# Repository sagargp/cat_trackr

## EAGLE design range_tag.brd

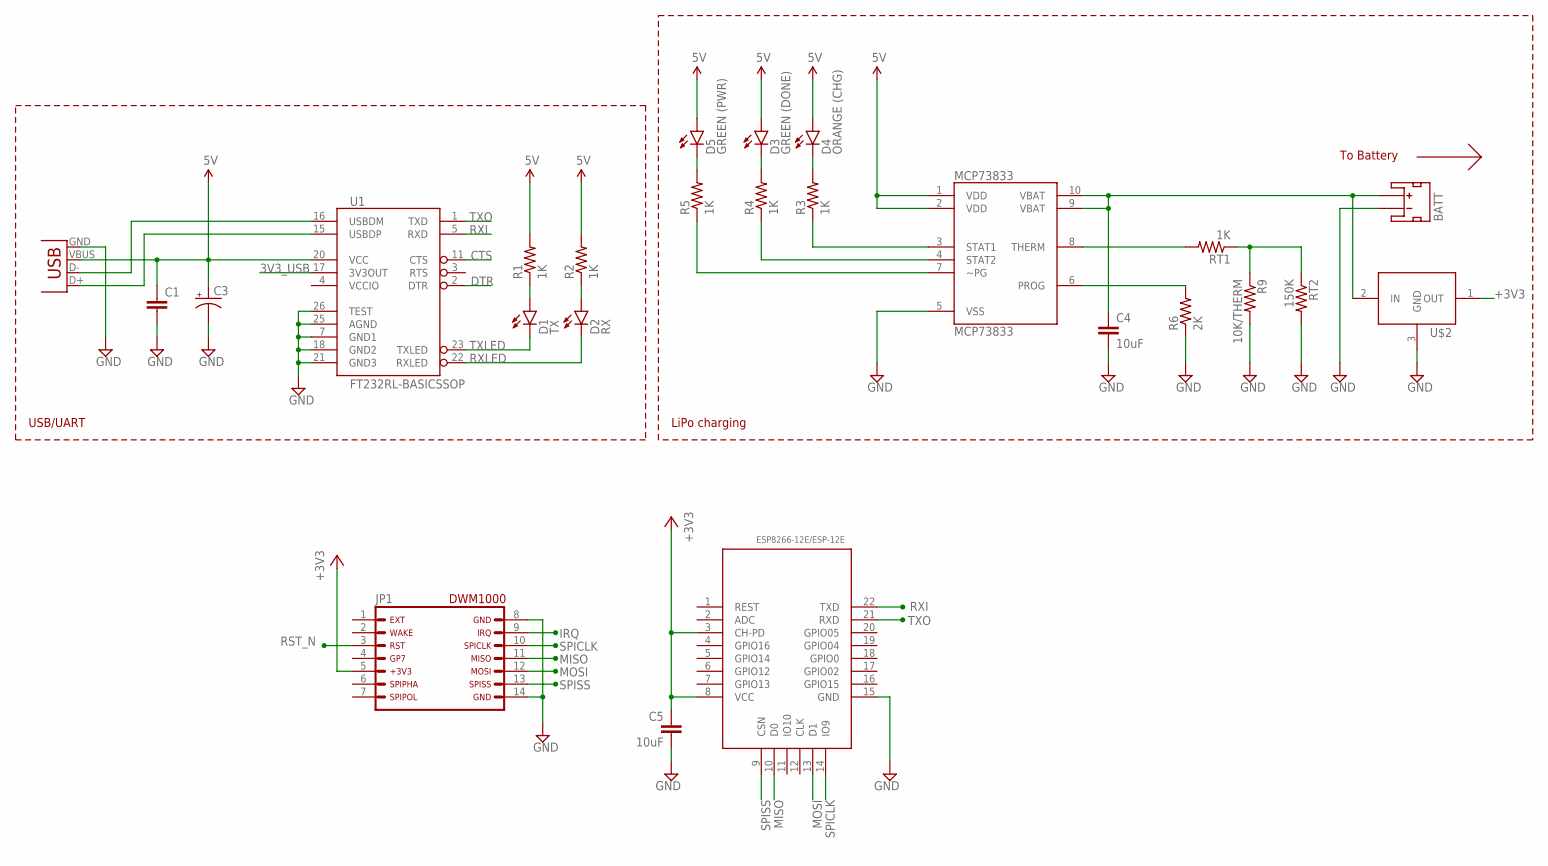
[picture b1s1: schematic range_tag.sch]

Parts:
BATT: JST_2MM_MALE; JST-2-SMD
C1: CAP0805; 0805
C3: CAP_POL1206-KIT; EIA3216-KIT
C4, C5: 10uF; 1206
D1: TX; LED-1206
D2: RX; LED-1206
D3: GREEN (DONE); LED-1206
D4: ORANGE (CHG); LED-1206
D5: GREEN (PWR); LED-1206
JP1: DWM1000-DIPDWM1000-BREAKOUT; 2X07_HOLES_ONLY
JP2: USB-SMD-NS; USB-MINIB-NOSTOP
MCP73833: MCP73833; MSOP-10
R1, R2, R3, R4, R5: 1K; 1206
R6: 2K; 1206
R9: 10K/THERM; 1206
RT1: 1K; 1206
RT2: 150K; 1206
U1: FT232RL-BASICSSOP; SSOP28DB
U3: ESP8266-12E/ESP-12E; LGA22-2.0-24X16MM
U$2: LM3480IM4; SOT23-3

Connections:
3V3_USB: U1.17 (3V3OUT)
5V: C1.1, C3.A (+), D3.A, D4.A, D5.A, JP2.VBUS, MCP73833.1 (VDD), MCP73833.2 (VDD), R1.2, R2.2, U1.20 (VCC)
+3V3: C5.1, JP1.5, U3.3 (CH-PD), U3.8 (VCC), U$2.1 (OUT)
CTS: U1.11 (CTS)
DTR: U1.2 (DTR)
GND: BATT.1 (-), C1.2, C3.C (-), C4.2, C5.2, JP1.8, JP1.14, JP2.GND, MCP73833.5 (VSS), R6.1, R9.2, RT2.2, U1.7 (GND1), U1.18 (GND2), U1.21 (GND3), U1.25 (AGND), U1.26 (TEST), U3.15 (GND), U$2.3 (GND)
IRQ: JP1.9
MISO: JP1.11, U3.10 (D0)
MOSI: JP1.12, U3.13 (D1)
unnamed: MCP73833.8 (THERM), RT1.2
unnamed: R9.1, RT1.1, RT2.1
unnamed: D3.C, R4.2
unnamed: D4.C, R3.2
unnamed: D1.A, R1.1
unnamed: D2.A, R2.1
unnamed: D5.C, R5.2
unnamed: MCP73833.6 (PROG), R6.2
N_PG: MCP73833.7 (~PG), R5.1
RST_N: JP1.3
RXI: U1.5 (RXD), U3.22 (TXD)
RXLED: D2.C, U1.22 (RXLED)
SPICLK: JP1.10, U3.14 (IO9)
SPISS: JP1.13, U3.9 (CSN)
STAT1: MCP73833.3 (STAT1), R3.1
STAT2: MCP73833.4 (STAT2), R4.1
TXLED: D1.C, U1.23 (TXLED)
TXO: U1.1 (TXD), U3.21 (RXD)
USBDM: JP2.D-, U1.16 (USBDM)
USBDP: JP2.D+, U1.15 (USBDP)
VCCIO: U1.4 (VCCIO)
V_BATT: BATT.2 (+), C4.1, MCP73833.9 (VBAT), MCP73833.10 (VBAT), U$2.2 (IN)

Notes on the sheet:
USB/UART
LiPo charging
To Battery

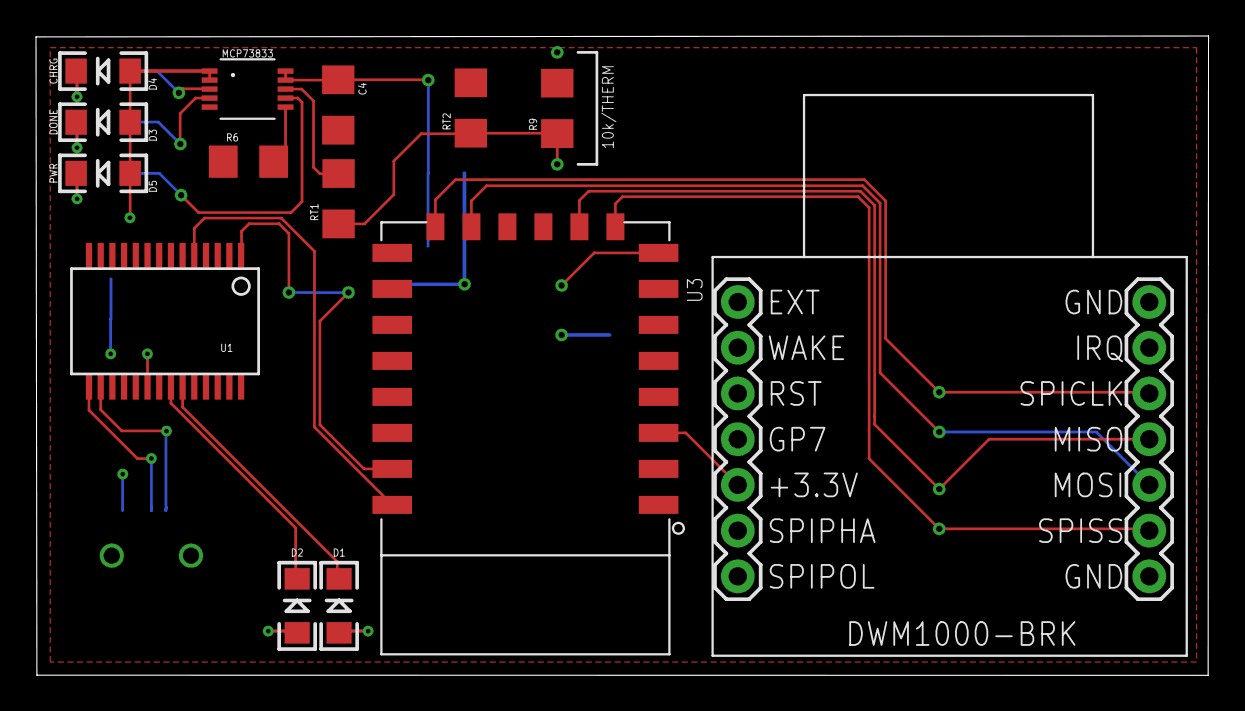
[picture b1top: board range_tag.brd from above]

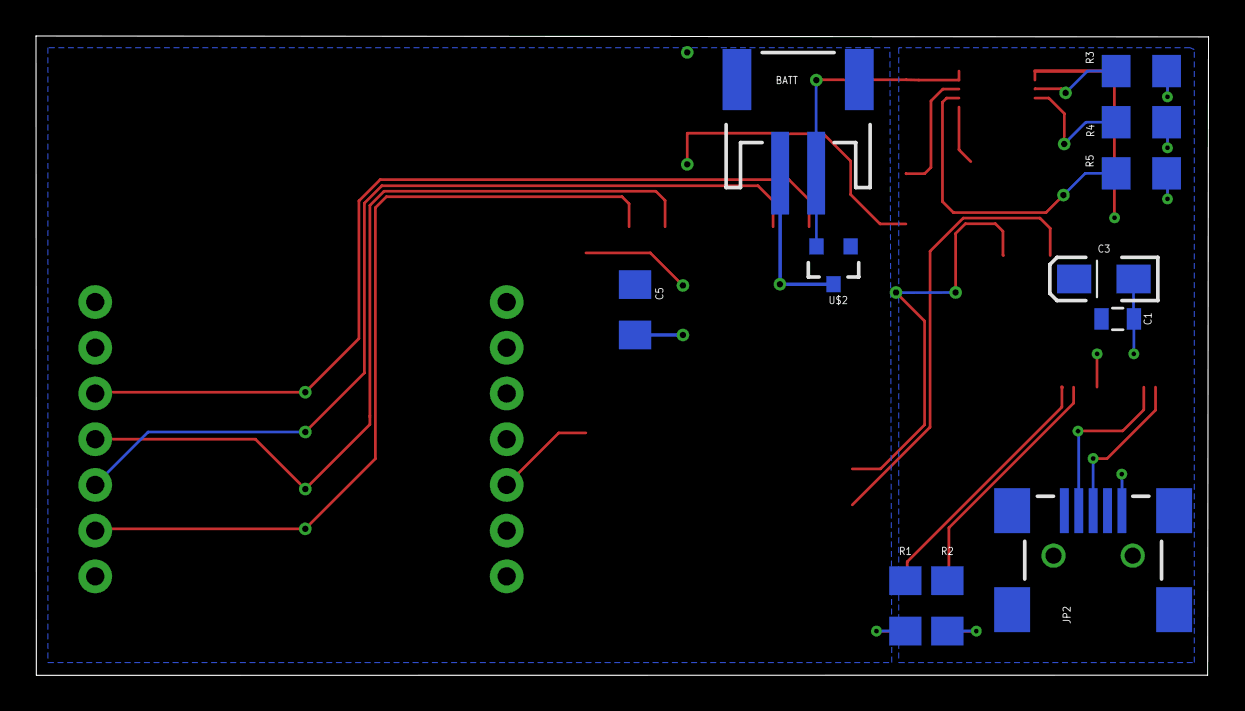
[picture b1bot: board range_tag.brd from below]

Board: 2 copper layers, 65.1 x 35.5 mm, 25 parts (11 on the bottom side), 25 nets.

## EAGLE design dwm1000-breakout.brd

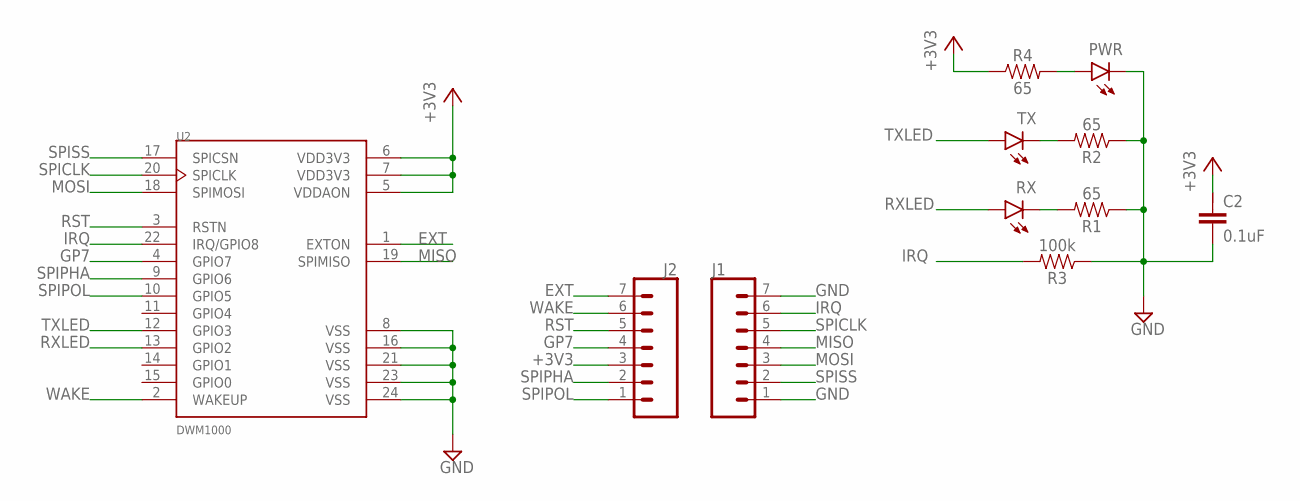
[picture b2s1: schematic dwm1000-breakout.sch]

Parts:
C2: 0.1uF; C1210; DIGIKEY_PARTNUM 1276-2854-1-ND
J1, J2: CONN_07LOCK; 1X07_LOCK; DIGIKEY_PARTNUM A26509-07-ND
PWR: GREEN; LED-1206; DIGIKEY_PARTNUM 350-2053-1-ND
R1, R2, R4: 65; 1206; DIGIKEY_PARTNUM 311-64.9FRCT-ND
R3: 100k; 1206; DIGIKEY_PARTNUM 311-100KERCT-ND
RX: GREEN; LED-1206; DIGIKEY_PARTNUM 350-2053-1-ND
TX: GREEN; LED-1206
U2: DWM1000; XCVR_DWM1000; DIGIKEY_PARTNUM 1479-1002-1-ND

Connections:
+3V3: C2.P$1, J2.3, R4.1, U2.5 (VDDAON), U2.6 (VDD3V3), U2.7 (VDD3V3)
EXT: J2.7, U2.1 (EXTON)
GND: C2.P$2, J1.1, J1.7, PWR.C, R1.1, R2.1, R3.1, U2.8 (VSS), U2.16 (VSS), U2.21 (VSS), U2.23 (VSS), U2.24 (VSS)
GP7: J2.4, U2.4 (GPIO7)
IRQ: J1.6, R3.2, U2.22 (IRQ/GPIO8)
MISO: J1.4, U2.19 (SPIMISO)
MOSI: J1.3, U2.18 (SPIMOSI)
unnamed: R1.2, RX.C
unnamed: R2.2, TX.C
unnamed: PWR.A, R4.2
RST: J2.5, U2.3 (RSTN)
RXLED: RX.A, U2.13 (GPIO2)
SPICLK: J1.5, U2.20 (SPICLK)
SPIPHA: J2.2, U2.9 (GPIO6)
SPIPOL: J2.1, U2.10 (GPIO5)
SPISS: J1.2, U2.17 (SPICSN)
TXLED: TX.A, U2.12 (GPIO3)
WAKE: J2.6, U2.2 (WAKEUP)

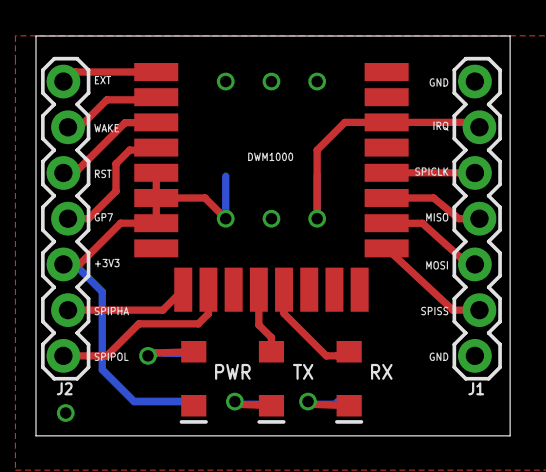
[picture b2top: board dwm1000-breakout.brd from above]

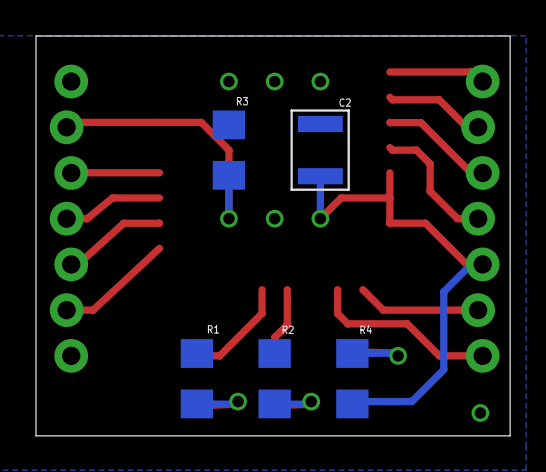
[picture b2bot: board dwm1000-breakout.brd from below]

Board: 2 copper layers, 26.3 x 22.2 mm, 11 parts (5 on the bottom side), 18 nets.

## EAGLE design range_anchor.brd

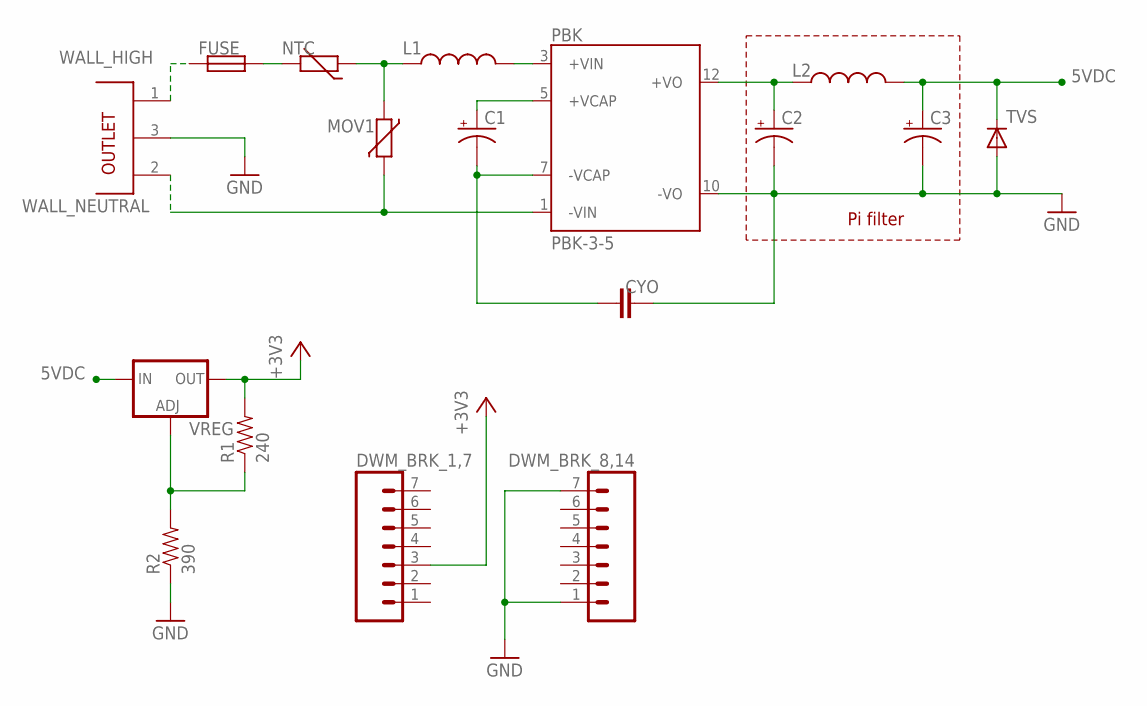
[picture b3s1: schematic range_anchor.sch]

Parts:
C1, C2, C3: CAP_POLPTH2; CPOL-RADIAL-10UF-25V
CYO: CAPPTH3; CAP-PTH-LARGE
DWM_BRK_1,7, DWM_BRK_8,14: M07LOCK; 1X07_LOCK
FUSE: FUSESMD; 2-SMD
L1, L2: INDUCTORAXIAL-0.6; AXIAL-0.6
MOV1: VARISTOR-2,5; R-5
NTC: THERMISTOR-7,5; R-7,5
PBK: PBK-3-5; 3-5-VERTICAL
R1: 240; 1206
R2: 390; 1206
TVS: DIODE-DO214AA; DO214AA
VREG: V_REG_317DPACK; V-REG_DPACK
WALL: OUTLET

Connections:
3V3: DWM_BRK_1,7.3, R1.2, VREG.4 (OUT)
5VDC: C3.1 (+), L2.P$2 (2), TVS.C, VREG.3 (IN)
GND: C2.2 (-), C3.2 (-), CYO.2, DWM_BRK_8,14.1, DWM_BRK_8,14.7, PBK.10 (-VO), R2.1, TVS.A, WALL.3 (GND)
unnamed: FUSE.2, NTC.2
unnamed: L1.P$1 (1), MOV1.1, NTC.1
unnamed: L1.P$2 (2), PBK.3 (+VIN)
unnamed: C1.1 (+), PBK.5 (+VCAP)
unnamed: C1.2 (-), CYO.1, PBK.7 (-VCAP)
unnamed: R1.1, R2.2, VREG.1 (ADJ)
unnamed: C2.1 (+), L2.P$1 (1), PBK.12 (+VO)
WALL_HIGH: FUSE.1, WALL.1 (HIGH)
WALL_NEUTRAL: MOV1.2, PBK.1 (-VIN), WALL.2 (NEUTRAL)

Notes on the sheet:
Pi filter

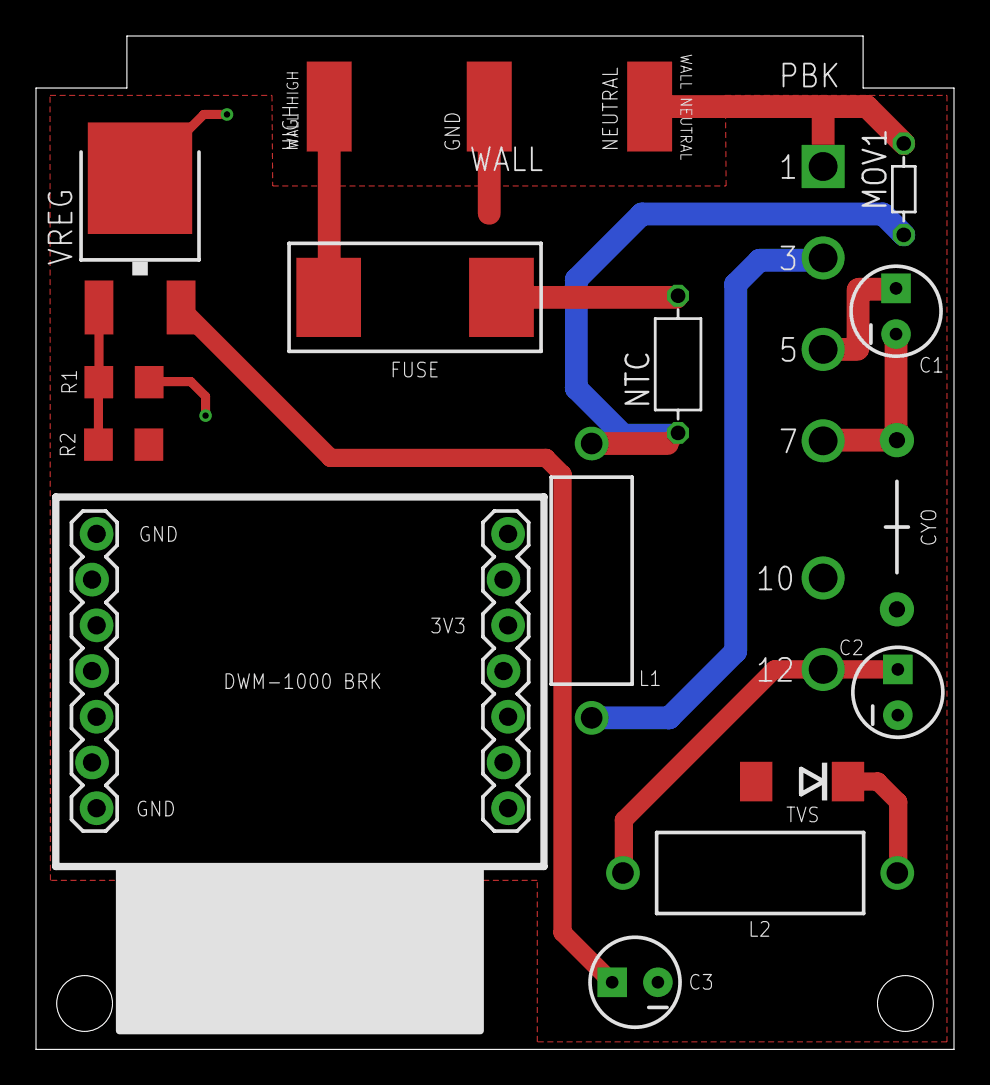
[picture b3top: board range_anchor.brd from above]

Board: 2 copper layers, 51.0 x 56.3 mm, 17 parts (0 on the bottom side), 12 nets.

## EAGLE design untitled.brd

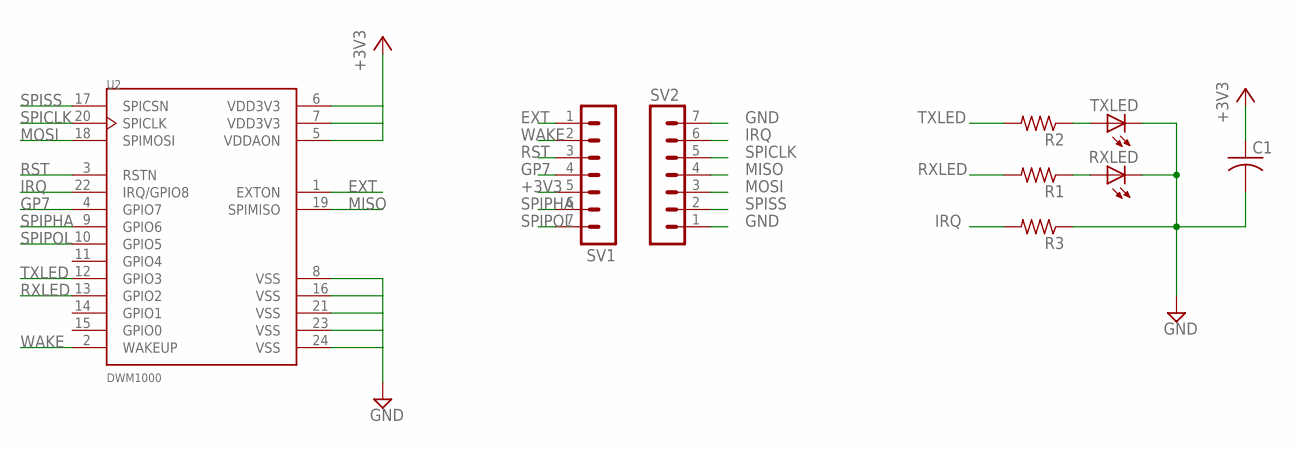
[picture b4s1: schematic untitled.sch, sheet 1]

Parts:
C1: C-USC1206; C1206
R1, R2, R3: R-US_R1206; R1206
RXLED: LEDSMT1206; 1206
SV1, SV2: MA07-1
TXLED: LEDSMT1206; 1206
U2: DWM1000; XCVR_DWM1000

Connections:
+3V3: C1.1, SV1.5, U2.5 (VDDAON), U2.6 (VDD3V3), U2.7 (VDD3V3)
EXT: SV1.1, U2.1 (EXTON)
GND: C1.2, R3.1, RXLED.C, SV2.1, SV2.7, TXLED.C, U2.8 (VSS), U2.16 (VSS), U2.21 (VSS), U2.23 (VSS), U2.24 (VSS)
GP7: SV1.4, U2.4 (GPIO7)
IRQ: R3.2, SV2.6, U2.22 (IRQ/GPIO8)
MISO: SV2.4, U2.19 (SPIMISO)
MOSI: SV2.3, U2.18 (SPIMOSI)
unnamed: R1.1, RXLED.A
unnamed: R2.1, TXLED.A
RST: SV1.3, U2.3 (RSTN)
RXLED: R1.2, U2.13 (GPIO2)
SPICLK: SV2.5, U2.20 (SPICLK)
SPIPHA: SV1.6, U2.9 (GPIO6)
SPIPOL: SV1.7, U2.10 (GPIO5)
SPISS: SV2.2, U2.17 (SPICSN)
TXLED: R2.2, U2.12 (GPIO3)
WAKE: SV1.2, U2.2 (WAKEUP)

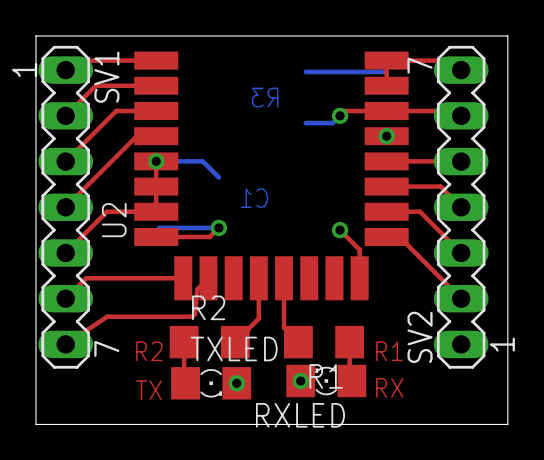
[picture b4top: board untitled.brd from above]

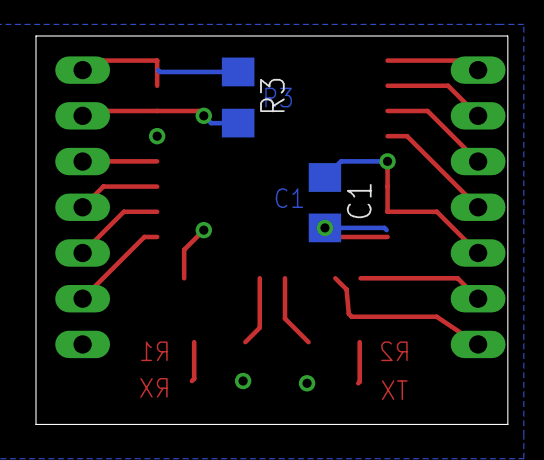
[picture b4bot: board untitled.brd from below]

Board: 2 copper layers, 26.2 x 21.6 mm, 9 parts (2 on the bottom side), 17 nets.

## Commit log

2017-06-24 Frist
2017-06-25 renamed and laid out a little better i hope
2017-06-25 used oshpark's DRU file
2017-06-25 added a power indicator LED
2017-06-25 Rand's nitpicking
2017-06-25 Whoops left some things unconnected. Fixed.
2017-06-26 Committing the datasheets
2017-06-27 Added part info
2017-07-25 Adding anchor board
2017-07-25 more

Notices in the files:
parts and their libraries:
SparkFun-Connectors: Licensing: Creative Commons ShareAlike 4.0 International - https://creativecommons.org/licenses/by-sa/4.0
